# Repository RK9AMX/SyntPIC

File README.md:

# SyntPIC
HF synthesizer Si5351A and PIC16F1787

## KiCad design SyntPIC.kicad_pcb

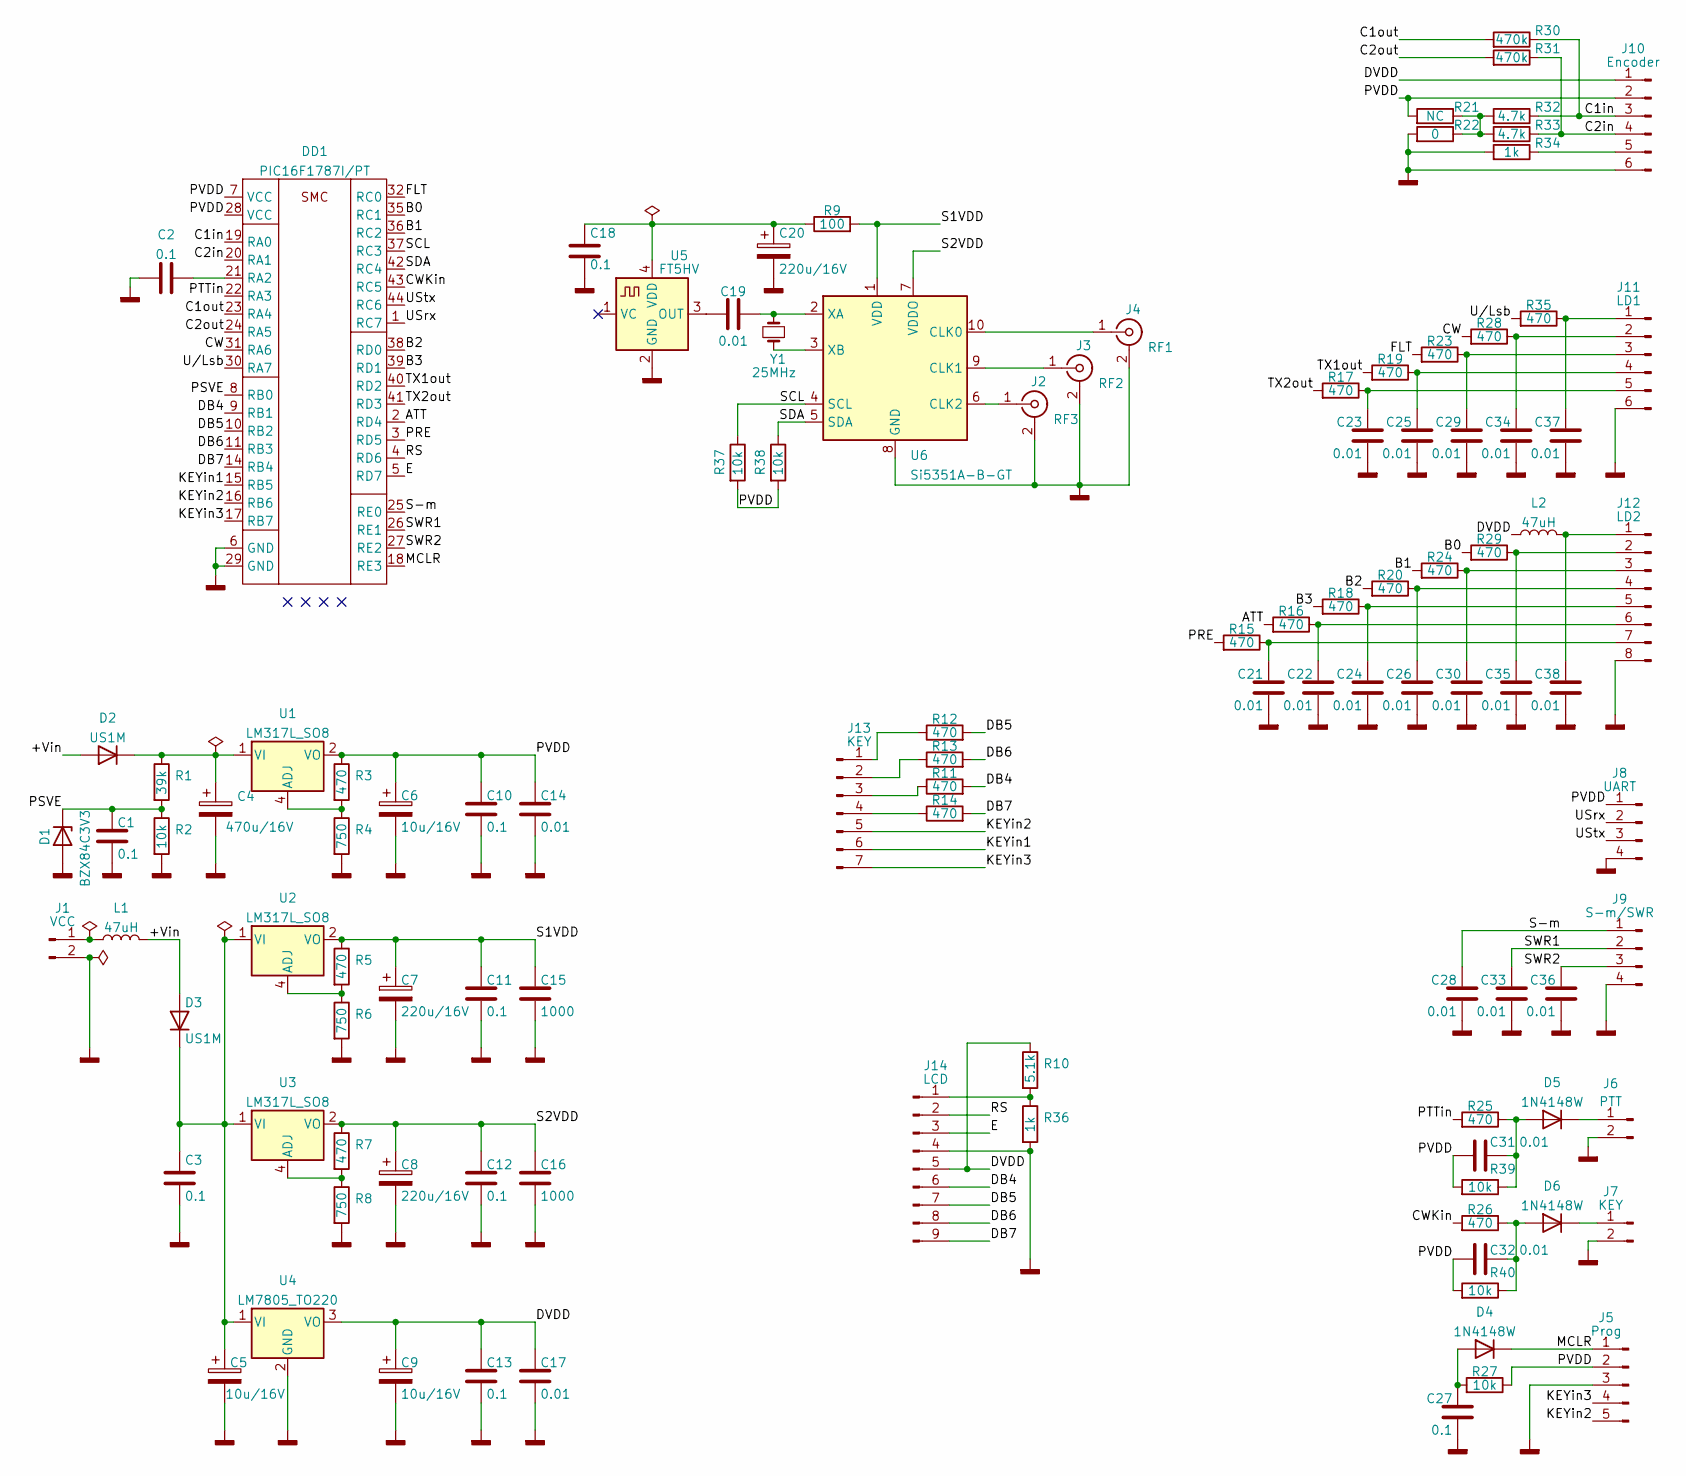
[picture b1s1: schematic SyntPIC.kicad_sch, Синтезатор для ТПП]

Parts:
C1, C2, C3, C10, C11, C12, C13, C18, C27: 0.1; C_0805_2012Metric_Pad1.18x1.45mm_HandSolder
C4: 470u/16V; CP_Elec_10x10
C5, C6, C9: 10u/16V; CP_EIA-6032-28_Kemet-C_Pad2.25x2.35mm_HandSolder
C7, C8, C20: 220u/16V; CP_Elec_6.3x7.7
C14, C17, C19, C21, C22, C23, C24, C25, C26, C28, C29, C30, C31, C32, C33, C34, C35, C36, C37, C38: 0.01; C_0805_2012Metric_Pad1.18x1.45mm_HandSolder
C15, C16: 1000; C_0805_2012Metric_Pad1.18x1.45mm_HandSolder
D1: BZX84C3V3; D_SOT-23_ANK
D2, D3: US1M; D_SMA
D4, D5, D6: 1N4148W; D_SOD-123
DD1: PIC16F1787I/PT; LQFP-44_10x10mm_P0.8mm
J1: VCC; PinHeader_1x02_P2.54mm_Vertical
J2: RF3; SMA_Wurth_60312002114503_Vertical
J3: RF2; SMA_Wurth_60312002114503_Vertical
J4: RF1; SMA_Wurth_60312002114503_Vertical
J5: Prog; PinHeader_1x05_P2.54mm_Vertical
J6: PTT; PinHeader_1x02_P2.54mm_Vertical
J7: KEY; PinHeader_1x02_P2.54mm_Vertical
J8: UART; PinHeader_1x04_P2.54mm_Vertical
J9: S-m/SWR; PinHeader_1x04_P2.54mm_Vertical
J10: Encoder; PinHeader_1x06_P2.54mm_Vertical
J11: LD1; PinHeader_1x06_P2.54mm_Vertical
J12: LD2; PinHeader_1x08_P2.54mm_Vertical
J13: KEY; PinHeader_1x07_P2.54mm_Vertical
J14: LCD; PinHeader_1x09_P2.54mm_Vertical
L1, L2: 47uH; L_Radial_D8.7mm_P5.00mm_Fastron_07HCP
R1: 39k; R_0805_2012Metric_Pad1.20x1.40mm_HandSolder
R2, R27, R37, R38, R39, R40: 10k; R_0805_2012Metric_Pad1.20x1.40mm_HandSolder
R3, R5, R7, R11, R12, R13, R14, R15, R16, R17, R18, R19, R20, R23, R24, R25, R26, R28, R29, R35: 470; R_0805_2012Metric_Pad1.20x1.40mm_HandSolder
R4, R6, R8: 750; R_0805_2012Metric_Pad1.20x1.40mm_HandSolder
R9: 100; R_0805_2012Metric_Pad1.20x1.40mm_HandSolder
R10: 5.1k; R_0805_2012Metric_Pad1.20x1.40mm_HandSolder
R21: NC; R_0805_2012Metric_Pad1.20x1.40mm_HandSolder
R22: 0; R_0805_2012Metric_Pad1.20x1.40mm_HandSolder
R30, R31: 470k; R_0805_2012Metric_Pad1.20x1.40mm_HandSolder
R32, R33: 4.7k; R_0805_2012Metric_Pad1.20x1.40mm_HandSolder
R34, R36: 1k; R_0805_2012Metric_Pad1.20x1.40mm_HandSolder
U1, U2, U3: LM317L_SO8; SOIC-8_3.9x4.9mm_P1.27mm
U4: LM7805_TO220; TO-220-3_Horizontal_TabDown
U5: FT5HV; Oscillator_SMD_Fox_FT5H_5.0x3.2mm
U6: Si5351A-B-GT; MSOP-10_3x3mm_P0.5mm
Y1: 25MHz; Crystal_HC49-4H_Vertical

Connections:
/+Vin: D2.2 (A), D3.2 (A), L1.2
/ATT: DD1.2 (RD4), R16.2
/B0: DD1.35 (RC1), R29.2
/B1: DD1.36 (RC2), R24.2
/B2: DD1.38 (RD0), R20.2
/B3: DD1.39 (RD1), R18.2
/C1in: DD1.19 (RA0), J10.3, R30.1, R32.1
/C1out: DD1.23 (RA4), R30.2
/C2in: DD1.20 (RA1), J10.4, R31.1, R33.1
/C2out: DD1.24 (RA5), R31.2
/CW: DD1.31 (RA6), R28.2
/CWKin: DD1.43 (RC5), R26.2
/DB4: DD1.9 (RB1), J14.6, R11.2
/DB5: DD1.10 (RB2), J14.7, R12.2
/DB6: DD1.11 (RB3), J14.8, R13.2
/DB7: DD1.14 (RB4), J14.9, R14.2
/DVDD: C9.1, C13.1, C17.1, J10.1, J14.5, L2.1, R10.1, U4.3 (VO)
/E: DD1.5 (RD7), J14.3
/FLT: DD1.32 (RC0), R23.2
/KEYin1: DD1.15 (RB5), J13.6
/KEYin2: DD1.16 (RB6), J5.5, J13.5
/KEYin3: DD1.17 (RB7), J5.4, J13.7
/MCLR: D4.1 (K), DD1.18 (RE3), J5.1
/PRE: DD1.3 (RD5), R15.2
/PSVE: C1.1, D1.1 (K), DD1.8 (RB0), R1.2, R2.1
/PTTin: DD1.22 (RA3), R25.2
/PVDD: C6.1, C10.1, C14.1, C31.2, C32.2, DD1.7 (VCC), DD1.28 (VCC), J5.2, J8.1, J10.2, R3.1, R21.2, R27.1, R37.2, R38.2, R39.2, R40.2, U1.2 (VO), U1.3 (VO), U1.6 (VO), U1.7 (VO)
/RS: DD1.4 (RD6), J14.2
/S1VDD: C7.1, C11.1, C15.1, R5.1, R9.2, U2.2 (VO), U2.3 (VO), U2.6 (VO), U2.7 (VO), U6.1 (VDD)
/S2VDD: C8.1, C12.1, C16.1, R7.1, U3.2 (VO), U3.3 (VO), U3.6 (VO), U3.7 (VO), U6.7 (VDDO)
/S-m: C28.1, DD1.25 (RE0), J9.1
/SCL: DD1.37 (RC3), R37.1, U6.4 (SCL)
/SDA: DD1.42 (RC4), R38.1, U6.5 (SDA)
/SWR1: C33.1, DD1.26 (RE1), J9.2
/SWR2: C36.1, DD1.27 (RE2), J9.3
/TX1out: DD1.40 (RD2), R19.2
/TX2out: DD1.41 (RD3), R17.2
/USrx: DD1.1 (RC7), J8.2
/UStx: DD1.44 (RC6), J8.3
/U/Lsb: DD1.30 (RA7), R35.2
GNDD: C1.2, C2.1, C3.2, C4.2, C5.2, C6.2, C7.2, C8.2, C9.2, C10.2, C11.2, C12.2, C13.2, C14.2, C15.2, C16.2, C17.2, C18.2, C20.2, C21.2, C22.2, C23.2, C24.2, C25.2, C26.2, C27.2, C28.2, C29.2, C30.2, C33.2, C34.2, C35.2, C36.2, C37.2, C38.2, D1.2 (A), DD1.6 (GND), DD1.29 (GND), J1.2, J2.2 (Ext), J3.2 (Ext), J4.2 (Ext), J5.3, J6.2, J7.2, J8.4, J9.4, J10.6, J11.6, J12.8, J14.4, R2.2, R4.2, R6.2, R8.2, R22.2, R34.2, R36.2, U4.2 (GND), U5.2 (GND), U6.8 (GND)
unnamed: C2.2, DD1.21 (RA2)
unnamed: C3.1, C5.1, D3.1 (K), U2.1 (VI), U3.1 (VI), U4.1 (VI)
unnamed: C4.1, D2.1 (K), R1.1, U1.1 (VI)
unnamed: C18.1, C20.1, R9.1, U5.4 (VDD)
unnamed: C19.1, U5.3 (OUT)
unnamed: C19.2, U6.2 (XA), Y1.2
unnamed: C21.1, J12.7, R15.1
unnamed: C22.1, J12.6, R16.1
unnamed: C23.1, J11.5, R17.1
unnamed: C24.1, J12.5, R18.1
unnamed: C25.1, J11.4, R19.1
unnamed: C26.1, J12.4, R20.1
unnamed: C27.1, D4.2 (A), R27.2
unnamed: C29.1, J11.3, R23.1
unnamed: C30.1, J12.3, R24.1
unnamed: C31.1, D5.2 (A), R25.1, R39.1
unnamed: C32.1, D6.2 (A), R26.1, R40.1
unnamed: C34.1, J11.2, R28.1
unnamed: C35.1, J12.2, R29.1
unnamed: C37.1, J11.1, R35.1
unnamed: C38.1, J12.1, L2.2
unnamed: D5.1 (K), J6.1
unnamed: D6.1 (K), J7.1
unnamed: J1.1, L1.1
unnamed: J2.1 (In), U6.6 (CLK2)
unnamed: J3.1 (In), U6.9 (CLK1)
unnamed: J4.1 (In), U6.10 (CLK0)
unnamed: J10.5, R34.1
unnamed: J13.1, R12.1
unnamed: J13.2, R13.1
unnamed: J13.3, R11.1
unnamed: J13.4, R14.1
unnamed: J14.1, R10.2, R36.1
unnamed: R3.2, R4.1, U1.4 (ADJ)
unnamed: R5.2, R6.1, U2.4 (ADJ)
unnamed: R7.2, R8.1, U3.4 (ADJ)
unnamed: R21.1, R22.1, R32.2, R33.2
unnamed: U6.3 (XB), Y1.1

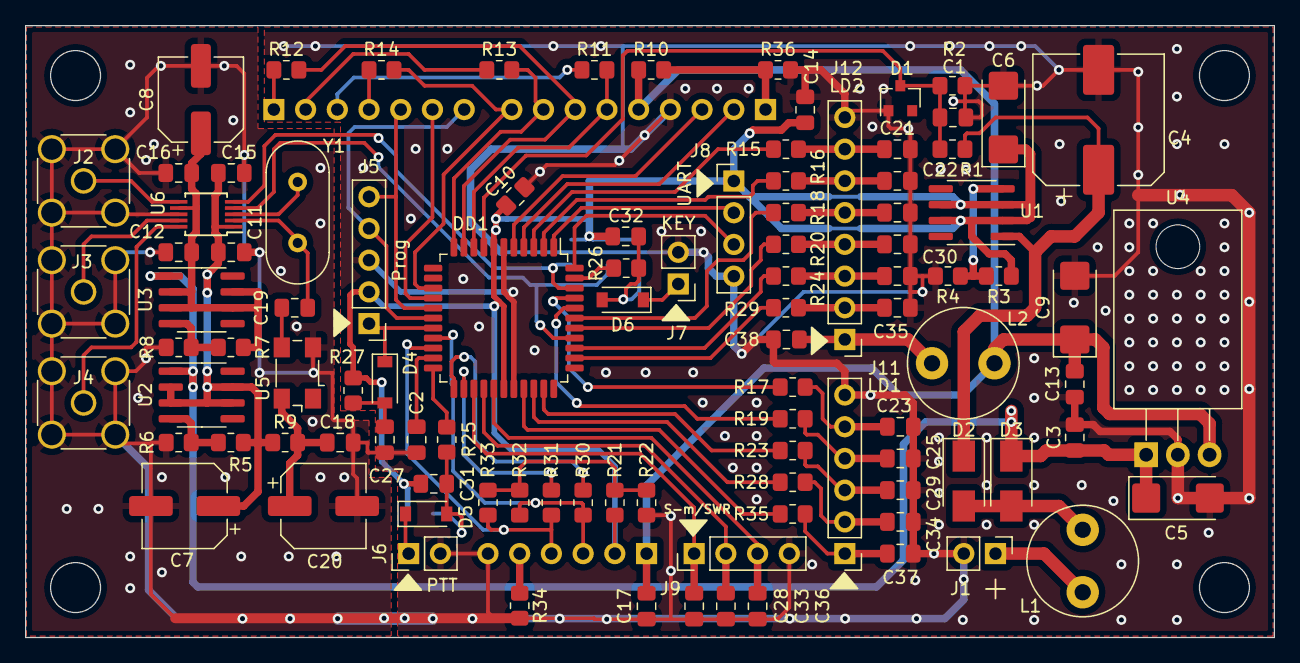
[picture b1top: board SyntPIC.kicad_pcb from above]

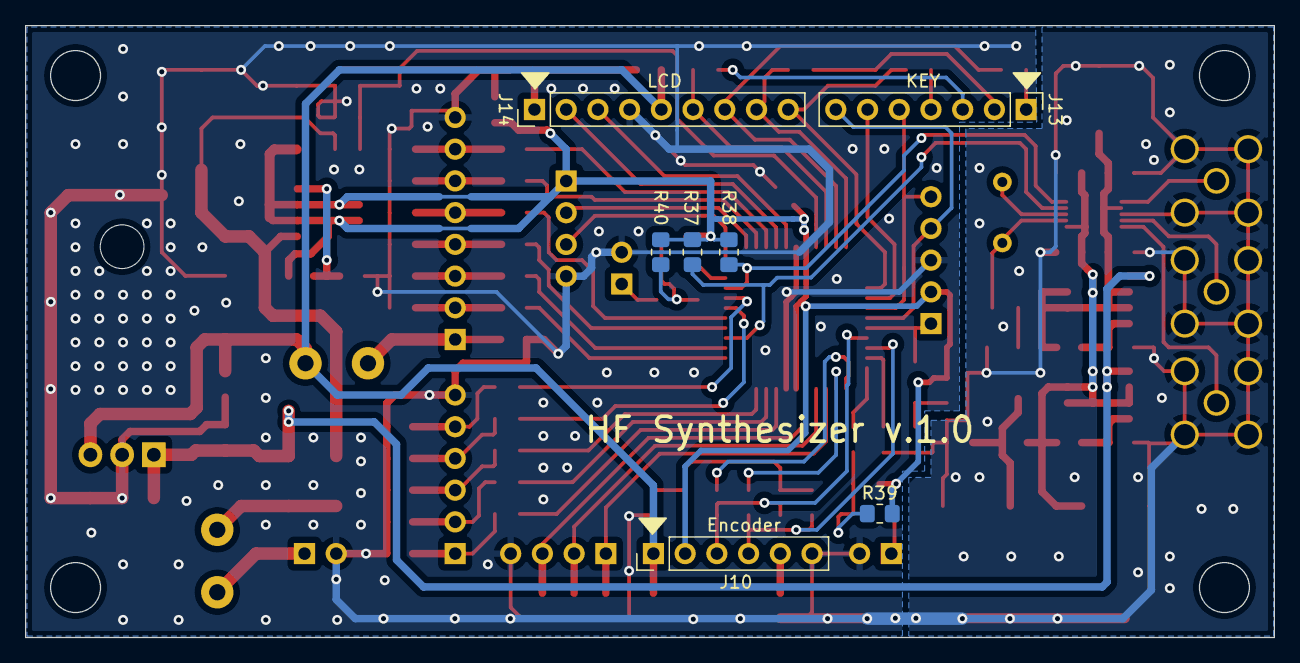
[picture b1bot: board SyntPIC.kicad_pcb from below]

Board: 2 copper layers, 100.0 x 49.0 mm, 108 parts (7 on the bottom side), 79 nets.

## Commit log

2023-01-11 Version 1.0
